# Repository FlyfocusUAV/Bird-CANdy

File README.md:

# Bird-CANdy

[![CC BY 4.0][cc-by-shield]][cc-by-sa] 

<hr>

PCB designed mainly as a universal [UAVCAN](https://uavcan.org/) sensor node which may also be used as a generic CAN interfacing device.

<br>

# What's UAVCAN Node? #
UAVCAN Node is a device that speaks UAVCAN protocol which is usually used to exchange data between autopilot (e.g. The Cube or Pixhawk running Ardupilot software)
and peripherals like GPS, Compass, LEDs, etc.

Since UAVCAN uses CAN inteface it allows for much longer wires than in case of I2C/SPI/UART/etc. and interference free data exchange due to the use of differential pairs.

# Advantages of Bird CANdy PCB #
PCB was designed with hobbyist, DIYers and researchers in mind.
* Fully Open Source Hardware for non-commercial use
* Only 2 copper layers for cheap production
* 3.3V or 5V selectable outputs
* JST-GH connectors (fully compatible with [The Cube Autopilot](https://github.com/proficnc/The-Cube))
* Supports all [Ardupilot](https://ardupilot.org/) peripherals like GPS, Compass, Baro, IMU, LEDs, etc, as well as PWM Servo output.

# What about the software? #
PCB can run [AP_Periph](https://github.com/ArduPilot/ardupilot/tree/master/Tools/AP_Periph) or your own software written for STM32 microcontroller.

# Pinout #

# Commercial license #
If You need a commercial license please send us an email to contact@flyfocus.pl 
<!-- 
 -->

[cc-by-sa]: https://creativecommons.org/licenses/by-sa/4.0/
[cc-by-shield]: https://img.shields.io/badge/License-CC%20BY%20%20SA%204.0-a8400e

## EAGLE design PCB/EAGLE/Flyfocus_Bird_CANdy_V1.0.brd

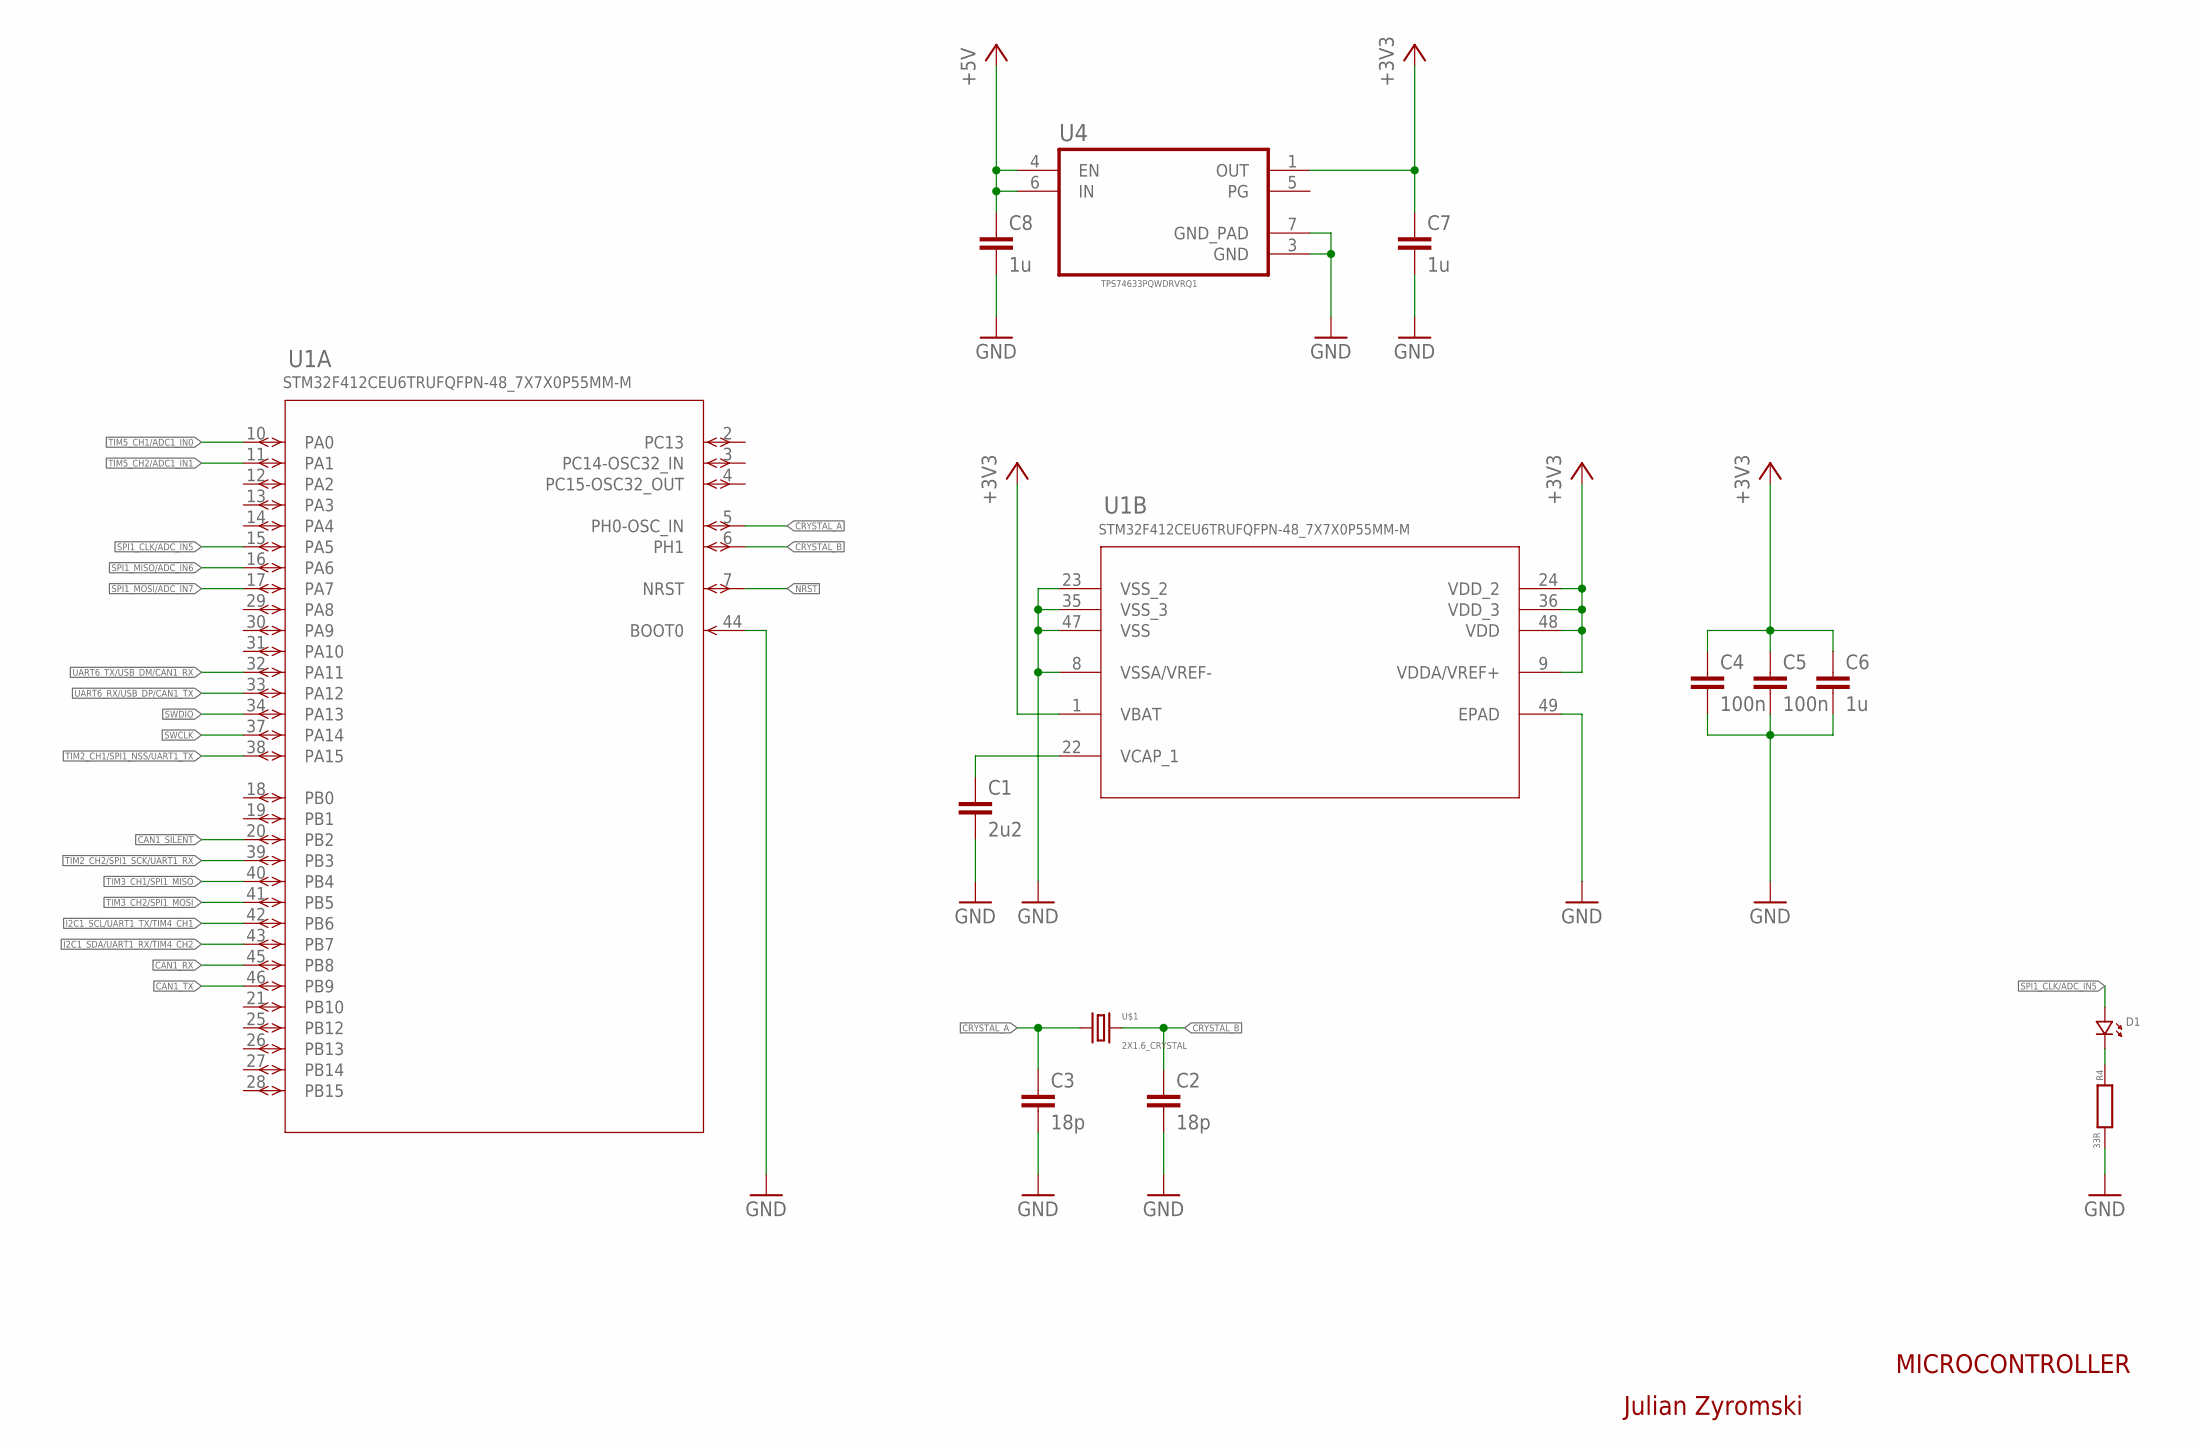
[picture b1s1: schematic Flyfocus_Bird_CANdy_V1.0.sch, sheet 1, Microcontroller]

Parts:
C1: 2u2; R0402
C2, C3: 18p; R0402
C4, C5: 100n; R0402
C6, C7, C8: 1u; R0402
D1: LED.0402; 0402.LED
R4: 33R; R0402
U1: STM32F412CEU6TRUFQFPN-48_7X7X0P55MM-M; UFQFPN-48_7X7X0P55MM-M
U4: TPS74633PQWDRVRQ1; SON65P200X200X80-7N
U$1: 2X1.6_CRYSTAL; OSC_FA-128_16MHZ

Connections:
+3V3: C4.1, C5.1, C6.1, C7.1, U1.1 (VBAT), U1.9 (VDDA/VREF+), U1.24 (VDD_2), U1.36 (VDD_3), U1.48 (VDD), U4.1 (OUT); also elsewhere on the board
+5V: C8.1, U4.4 (EN), U4.6 (IN); also elsewhere on the board
CAN1_RX: U1.45 (PB8); also elsewhere on the board
CAN1_SILENT: U1.20 (PB2); also elsewhere on the board
CAN1_TX: U1.46 (PB9); also elsewhere on the board
CRYSTAL_A: C3.1, U1.5 (PH0-OSC_IN), U$1.1
CRYSTAL_B: C2.1, U1.6 (PH1), U$1.3 (2)
GND: C1.2, C2.2, C3.2, C4.2, C5.2, C6.2, C7.2, C8.2, R4.2, U1.8 (VSSA/VREF-), U1.23 (VSS_2), U1.35 (VSS_3), U1.44 (BOOT0), U1.47 (VSS), U1.49 (EPAD), U4.3 (GND), U4.7 (GND_PAD); also elsewhere on the board
I2C1_SCL/UART1_TX/TIM4_CH1: U1.42 (PB6); also elsewhere on the board
I2C1_SDA/UART1_RX/TIM4_CH2: U1.43 (PB7); also elsewhere on the board
unnamed: C1.1, U1.22 (VCAP_1)
unnamed: D1.P$2 (2), R4.1
NRST: U1.7 (NRST); also elsewhere on the board
SPI1_CLK/ADC_IN5: D1.P$1 (1), U1.15 (PA5); also elsewhere on the board
SPI1_MISO/ADC_IN6: U1.16 (PA6); also elsewhere on the board
SPI1_MOSI/ADC_IN7: U1.17 (PA7); also elsewhere on the board
SWCLK: U1.37 (PA14); also elsewhere on the board
SWDIO: U1.34 (PA13); also elsewhere on the board
TIM2_CH1/SPI1_NSS/UART1_TX: U1.38 (PA15); also elsewhere on the board
TIM2_CH2/SPI1_SCK/UART1_RX: U1.39 (PB3); also elsewhere on the board
TIM3_CH1/SPI1_MISO: U1.40 (PB4); also elsewhere on the board
TIM3_CH2/SPI1_MOSI: U1.41 (PB5); also elsewhere on the board
TIM5_CH1/ADC1_IN0: U1.10 (PA0); also elsewhere on the board
TIM5_CH2/ADC1_IN1: U1.11 (PA1); also elsewhere on the board
UART6_RX/USB_DP/CAN1_TX: U1.33 (PA12); also elsewhere on the board
UART6_TX/USB_DM/CAN1_RX: U1.32 (PA11); also elsewhere on the board

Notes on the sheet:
Julian Zyromski
MICROCONTROLLER

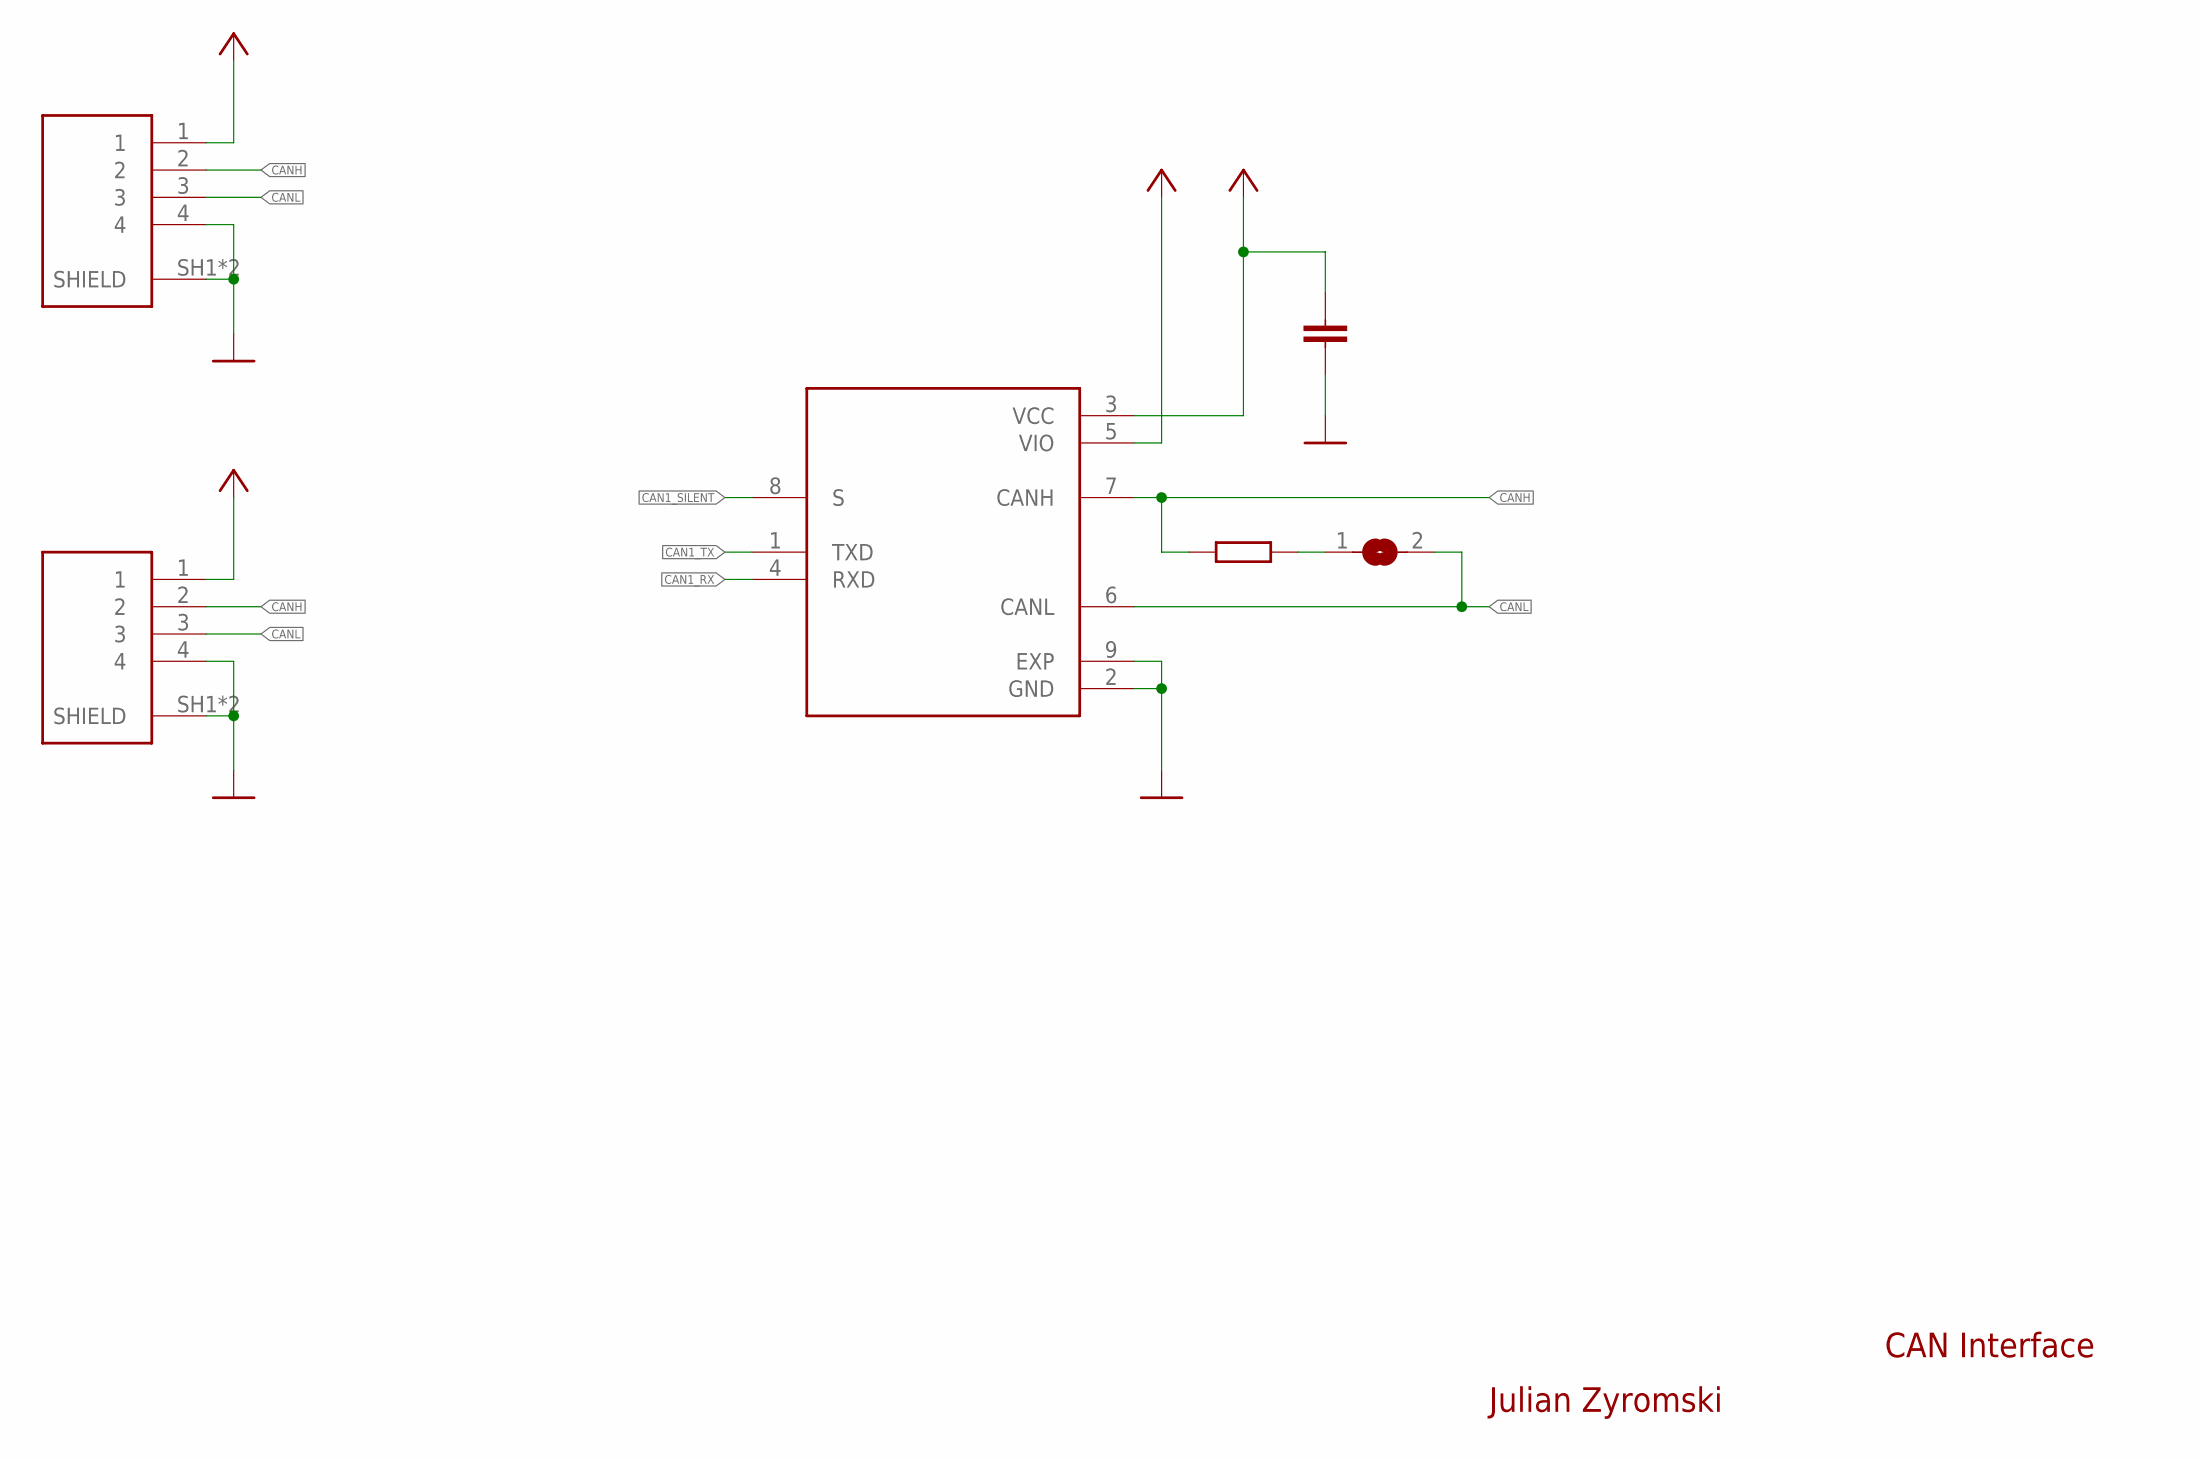
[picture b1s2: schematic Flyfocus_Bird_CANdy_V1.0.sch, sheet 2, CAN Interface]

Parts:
C9: 2u2; R0402
J1, J2: SM04B-GHS-TB(LF)(SN)-; JST_SM04B-GHS-TB(LF)(SN)-
R1: 120R/thick_film; 0603
SJ1: SJ
U2: TJA1051TK/3/1J; SON65P300X300X95-8N

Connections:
+3V3: U2.5 (VIO); also elsewhere on the board
+5V: C9.1, J1.1, J2.1, U2.3 (VCC); also elsewhere on the board
CAN1_RX: U2.4 (RXD); also elsewhere on the board
CAN1_SILENT: U2.8 (S); also elsewhere on the board
CAN1_TX: U2.1 (TXD); also elsewhere on the board
CANH: J1.2, J2.2, R1.P$1 (1), U2.7 (CANH); also elsewhere on the board
CANL: J1.3, J2.3, SJ1.2, U2.6 (CANL); also elsewhere on the board
GND: C9.2, J1.4, J1.SH1 (SHIELD), J1.SH2 (SHIELD), J2.4, J2.SH1 (SHIELD), J2.SH2 (SHIELD), U2.2 (GND), U2.9 (EXP); also elsewhere on the board
unnamed: R1.P$2 (2), SJ1.1

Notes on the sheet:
Julian Zyromski
CAN Interface

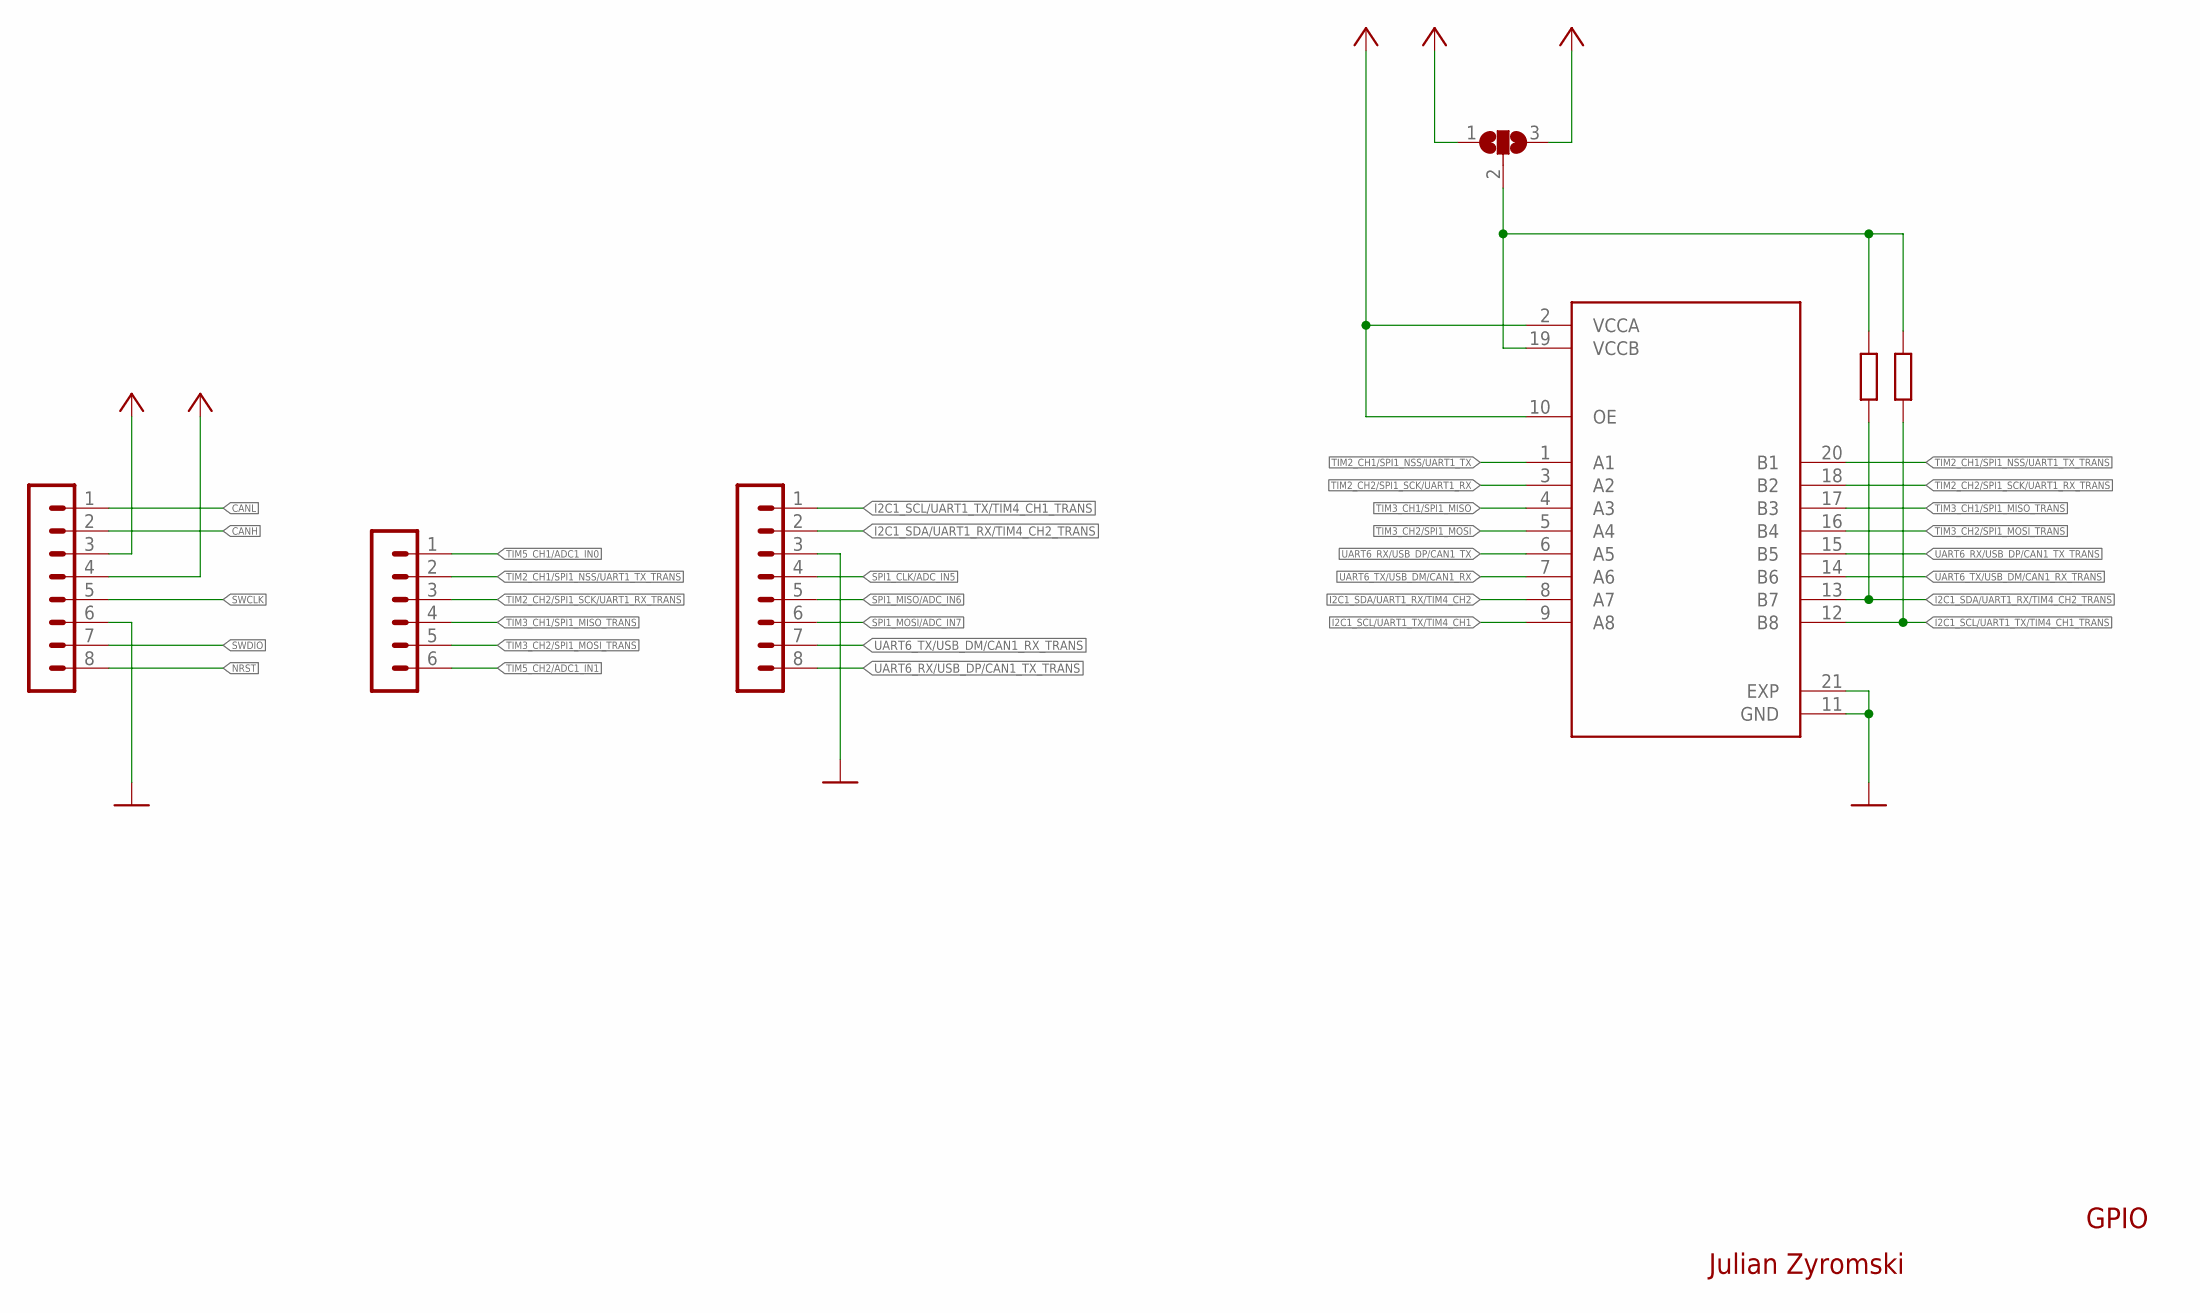
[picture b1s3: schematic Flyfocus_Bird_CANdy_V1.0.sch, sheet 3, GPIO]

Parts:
R2, R3: 4k7; R0402
SJ2: SJ2W; SJ_2
SV1, SV2: MA08-1
SV3: MA06-1
U3: TXS0108ERGYR; IC_TXS0108ERGYR

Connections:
+3V3: SJ2.1, SV1.4, U3.2 (VCCA), U3.10 (OE); also elsewhere on the board
+5V: SJ2.3, SV1.3; also elsewhere on the board
CANH: SV1.2; also elsewhere on the board
CANL: SV1.1; also elsewhere on the board
GND: SV1.6, SV2.3, U3.11 (GND), U3.21 (EXP); also elsewhere on the board
I2C1_SCL/UART1_TX/TIM4_CH1: U3.9 (A8); also elsewhere on the board
I2C1_SCL/UART1_TX/TIM4_CH1_TRANS: R3.1, SV2.1, U3.12 (B8)
I2C1_SDA/UART1_RX/TIM4_CH2: U3.8 (A7); also elsewhere on the board
I2C1_SDA/UART1_RX/TIM4_CH2_TRANS: R2.1, SV2.2, U3.13 (B7)
unnamed: R2.2, R3.2, SJ2.2, U3.19 (VCCB)
NRST: SV1.8; also elsewhere on the board
SPI1_CLK/ADC_IN5: SV2.4; also elsewhere on the board
SPI1_MISO/ADC_IN6: SV2.5; also elsewhere on the board
SPI1_MOSI/ADC_IN7: SV2.6; also elsewhere on the board
SWCLK: SV1.5; also elsewhere on the board
SWDIO: SV1.7; also elsewhere on the board
TIM2_CH1/SPI1_NSS/UART1_TX: U3.1 (A1); also elsewhere on the board
TIM2_CH1/SPI1_NSS/UART1_TX_TRANS: SV3.2, U3.20 (B1)
TIM2_CH2/SPI1_SCK/UART1_RX: U3.3 (A2); also elsewhere on the board
TIM2_CH2/SPI1_SCK/UART1_RX_TRANS: SV3.3, U3.18 (B2)
TIM3_CH1/SPI1_MISO: U3.4 (A3); also elsewhere on the board
TIM3_CH1/SPI1_MISO_TRANS: SV3.4, U3.17 (B3)
TIM3_CH2/SPI1_MOSI: U3.5 (A4); also elsewhere on the board
TIM3_CH2/SPI1_MOSI_TRANS: SV3.5, U3.16 (B4)
TIM5_CH1/ADC1_IN0: SV3.1; also elsewhere on the board
TIM5_CH2/ADC1_IN1: SV3.6; also elsewhere on the board
UART6_RX/USB_DP/CAN1_TX: U3.6 (A5); also elsewhere on the board
UART6_RX/USB_DP/CAN1_TX_TRANS: SV2.8, U3.15 (B5)
UART6_TX/USB_DM/CAN1_RX: U3.7 (A6); also elsewhere on the board
UART6_TX/USB_DM/CAN1_RX_TRANS: SV2.7, U3.14 (B6)

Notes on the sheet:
Julian Zyromski
GPIO

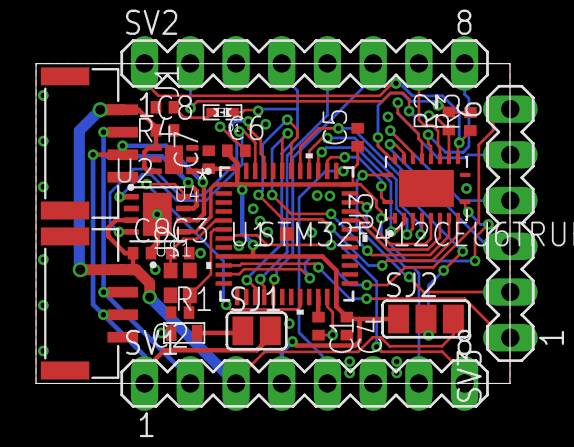
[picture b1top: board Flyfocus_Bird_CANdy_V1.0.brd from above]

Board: 2 copper layers, 26.3 x 17.8 mm, 26 parts (0 on the bottom side), 38 nets.

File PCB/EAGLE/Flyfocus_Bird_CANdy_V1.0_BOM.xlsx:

Item # | Designator | QTY | Mfg Part # | Value/Description | Package
1 | C4,C5 | 2 | generic MLCC capacitor | 100n | 0402
2 | R1 | 1 | smd thick film >=0.2W resistor | 120R thick film: >=0.2W | 0603
3 | C2,C3 | 2 | generic MLCC capacitor | 10p | 0402
4 | C6, C7, C8 | 3 | generic MLCC capacitor | 1u | 0402
5 | U$1 | 1 | ABM11AIG-16.000MHZ-8-1Z-T or similar | 16MHZ | 2x1.6mm crystal
6 | C1,C9 | 2 | generic MLCC capacitor | 2u2 | 0402
7 | R2, R3 | 2 | generic smd resistor | 4k7 | 0402
8 | J1, J2 | 2 | SM04B-GHS-TB(LF)(SN) | JST-GH connector
9 | U1 | 1 | STM32F412CEU6/STM32F412CGU6 |  | 48-UFQFPN
10 | U2 | 1 | TJA1051TK/3/1J or TCAN1042HVDRBTQ1 |  | 8-VDFN
11 | U4 | 1 | TPS74633 |  | 6-WSON
12 | U3 | 1 | TXS0108ERGYR |  | 20-VFQFN
13 | D1 | 1 | generic 0402 LED - GREEN |  | 0402
14 | R4 | 1 | generic smd resistor | 33R | 0402

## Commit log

2021-07-29 Add license
2021-07-29 Add pinout graphic
2021-07-29 added eagle files and pdf schematic
2021-07-29 Added PCB production files
2021-07-29 KiCad init
2021-08-03 added 3D files, readme update
2021-08-03 readme update
2021-11-09 Eagle project imported to KiCad

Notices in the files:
parts and their libraries:
COPYRIGHT: Copyright (C) 2018 Accelerated Designs. All rights reserved
